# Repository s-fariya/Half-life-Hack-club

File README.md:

# Starbie

A small star-shaped desk pet. A tiny OLED screen shows a character that wanders around, and it reacts when you tilt the board, shake it, or press its two buttons. I designed the whole PCB myself in KiCad, following the Hack Club Starbie Week 1 guide.

## What it does

- **Button 1** opens a radial menu with four actions: NAP, PLAY, FEED and PET.
- **Tilting** the board moves a selector ball around the menu. The MPU6050 motion sensor reads the tilt.
- **Button 1 again** picks the highlighted action, and the pet reacts with a nap, hearts or a jump.
- **Button 2** shows or hides a stats screen with joy, energy and fullness, plus the room temperature and humidity from the DHT11.
- **Shaking** the board makes the pet wiggle.

## Hardware

| Part | Job |
| --- | --- |
| XIAO ESP32-C3 | the microcontroller (the brain) |
| 0.96 inch 128x64 I2C OLED | the screen |
| MPU6050 module | motion sensor for tilt and shake |
| DHT11 | temperature and humidity sensor |
| 2 x Cherry MX style switches | the two buttons |
| 10k resistor | pull-up on the DHT11 data line |

## How it is wired

| Part | XIAO pin |
| --- | --- |
| OLED and MPU6050 SDA | D4 |
| OLED and MPU6050 SCL | D5 |
| DHT11 data | D1 |
| Button 1 | D2 |
| Button 2 | D3 |

The OLED and the MPU6050 share the same two I2C wires. Everything runs on 3.3V, and the buttons connect their pin to GND when pressed.

## PCB design

- Custom star-shaped board outline on the Edge.Cuts layer
- Signal wires routed on the copper layers
- GND copper pour on the front layer, so all the ground pins connect together
- The design rules check (DRC) shows only 2 courtyard errors, which come from the supplied OLED footprint and do not affect the board

### Bill of Materials (BOM)

| Part | Description | Qty | Unit Price | Total Price | Vendor | Link |
| :--- | :--- | :---: | :---: | :---: | :---: | :---: |
| **XIAO ESP32-C3** | Microcontroller | 1 | $4.90 | $4.90 | Pcbx | [Buy on Pcbx](https://www.seeedstudio.com/Seeed-XIAO-ESP32C3-p-5431.html) |
| **GY-521 MPU-6050** | 6-Axis Gyro / Accelerometer | 1 | $1.98 | $1.98 | Daraz | [Buy on Daraz](https://www.daraz.pk//products/i254765267-s1471144211.html?spm=a2o42.cart.0.0.56f77d68KNJnwu&urlFlag=true) |
| **0.96 inch OLED Display** | I2C Display Module (128x64) | 1 | $2.52 | $2.52 | Daraz | [Buy on Daraz](https://www.daraz.pk//products/i1966086027-s14048854700.html?spm=a2o42.cart.0.0.56f77d68hnK9nB&urlFlag=true) |
| **Cherry MX Switches** | Key Switches | 1 | $3.19 | $3.19 | AliExpress | [Buy on AliExpress](https://www.aliexpress.us/item/3256810219228347.html) |
| **DHT11 Sensor** | Temperature & Humidity Sensor | 1 | $1.49 | $1.49 | Daraz | [Buy on Daraz](https://www.daraz.pk//products/i254765267-s1471144211.html?spm=a2o42.cart.0.0.56f77d68jeWAmE&urlFlag=true) |
| **10K Resistors (1/4W)** | Pull-up Resistors | 1 | $0.42 | $0.42 | Daraz | [Buy on Daraz](https://www.daraz.pk//products/i465392816-s2198965661.html?spm=a2o42.cart.0.0.22717d68aTIudk&urlFlag=true)) |
| **Custom PCB (Starbie)** | Fabricated Circuit Board | 1 | $5.70 | $5.70 | pcbx | [pcbx Website](https://www.pcbx.com/order/manufacturing/pcb)) |
| **Tax & Shipping** | Shipping / Fees for whole order | 1 | $9.00 | $9.00 | — | — |
| **Total** | | | | **$29.2** | | *(Using $29.2 of $30.00 Tier 1 Funding)* |

## Files

- `MyProject.kicad_sch`: schematic
- `MyProject.kicad_pcb`: board layout
- `MyProject.kicad_pro`: KiCad project file
- `gerbers.zip`: gerber and drill files, ready to send to a PCB manufacturer
- `Firmware/Starbie/Starbie.ino`: Arduino starter code from the guide (its pins already match my board)
- `Firmware/Starbie/Starbie.ino`: Arduino starter code from the guide (its pins already match my board)

## Status

The PCB design is finished and the gerber files are exported. I have not built the board yet, so the firmware is untested on my hardware. Next steps are getting the board made, assembling it, and uploading the code.

## Credits
Firmware and project design are based on the Starbie guide from Hack Club by SharKingStudios (MIT license): https://github.com/SharKingStudios/Starbie
I built the KiCad schematic and PCB layout following the guide.

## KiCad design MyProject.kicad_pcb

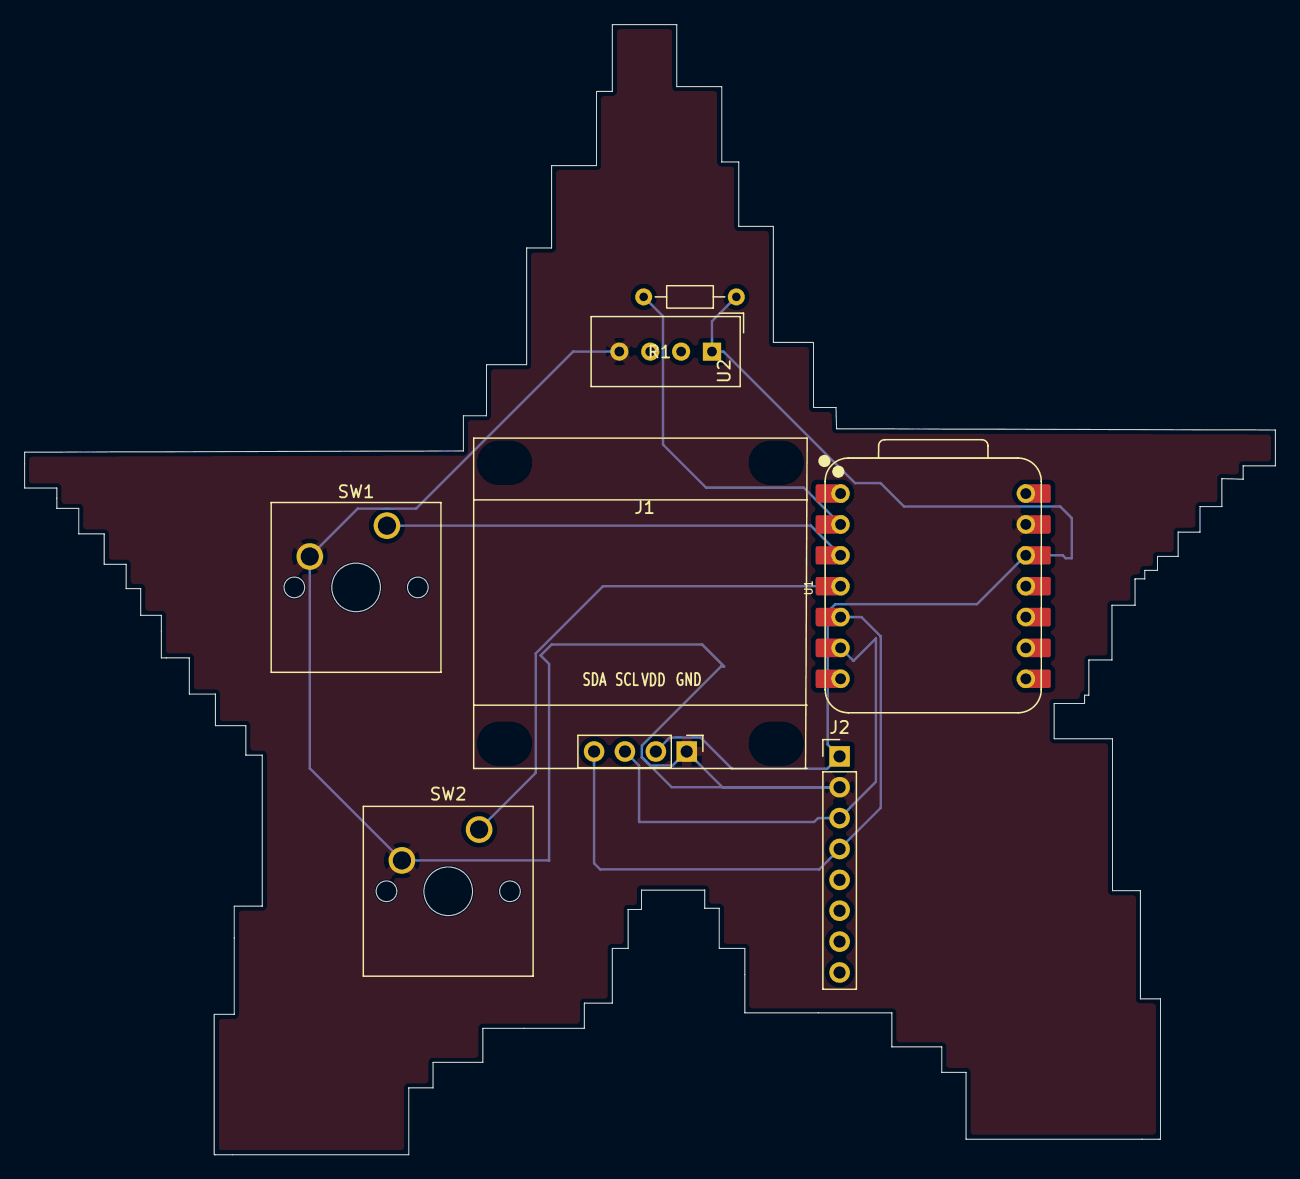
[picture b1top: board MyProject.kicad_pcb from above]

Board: 2 copper layers, 102.9 x 93.0 mm, 7 parts (0 on the bottom side), 7 nets.

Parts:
J1: Conn_01x04_Pin; Display_128x64_096_I2C
J2: Conn_01x08_Pin; PinHeader_1x08_P2.54mm_Vertical
R1: 10K; R_Axial_DIN0204_L3.6mm_D1.6mm_P7.62mm_Horizontal
SW1, SW2: SW_Push; SW_Cherry_MX_1.00u_PCB
U1: XIAO-ESP32-C3-SMD; XIAO-ESP32-C6-DIP
U2: DHT11; Aosong_DHT11_5.5x12.0_P2.54mm

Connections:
+3.3V: J1.2, J2.1, R1.1, U1.12 (3V3_OUT), U2.1 (VDD)
/DHT11 DATA: R1.2, U1.2 (D1)
/GPIO2: SW1.1, U1.3 (D2)
/GPIO3: SW2.1, U1.4 (D3)
/SCL: J1.3, J2.3, U1.6 (D5)
/SDA: J1.4, J2.4, U1.5 (D4)
GND: J1.1, J2.2, SW1.2, SW2.2, U1.13 (GND), U2.4 (GND)
